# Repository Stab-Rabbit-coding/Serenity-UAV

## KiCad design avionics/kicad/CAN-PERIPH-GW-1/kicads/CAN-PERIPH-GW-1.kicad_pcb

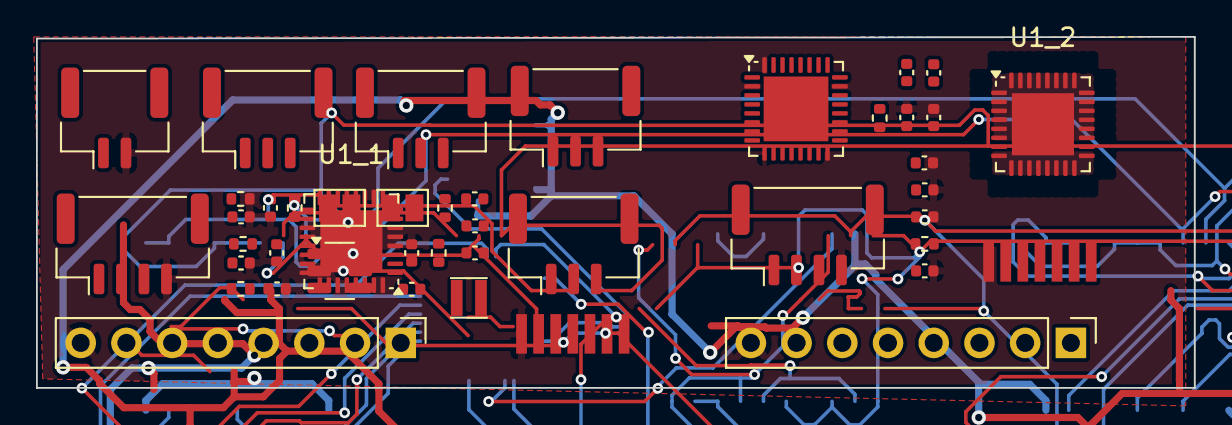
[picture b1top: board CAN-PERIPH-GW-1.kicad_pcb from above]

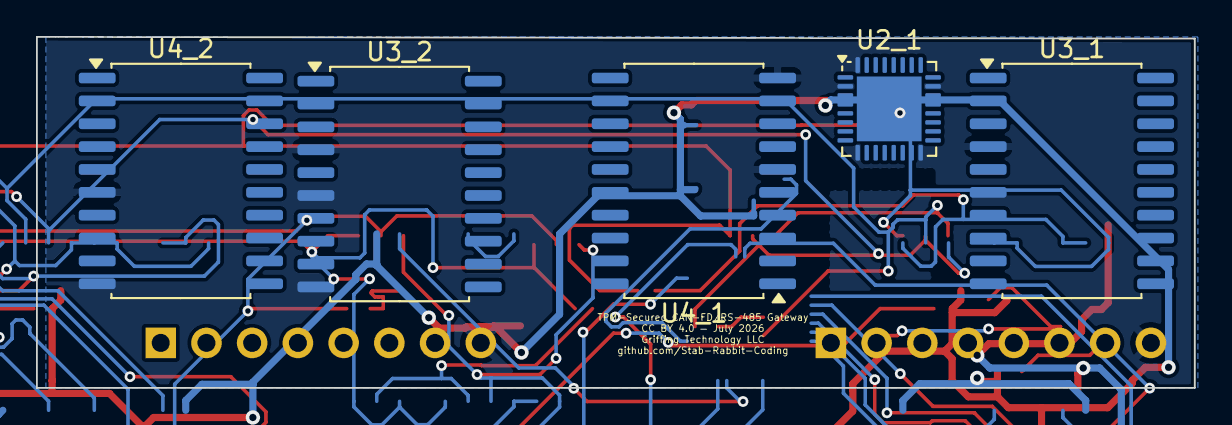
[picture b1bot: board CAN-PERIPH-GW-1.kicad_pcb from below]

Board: 2 copper layers, 64.3 x 19.5 mm, 49 parts (6 on the bottom side), 71 nets.

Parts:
C_IN: 10uF; C_0402_1005Metric
C_ISO1_1, C_ISO1_2: 100nF; C_0402_1005Metric
C_ISO2_1, C_ISO2_2: 1uF; C_0402_1005Metric
C_MCU1_1, C_MCU1_2: 100nF; C_0402_1005Metric
C_OUT: 22uF; C_0402_1005Metric
C_RS1_1, C_RS1_2, C_RS2_1, C_RS2_2: 100nF; C_0402_1005Metric
C_TPM1_1, C_TPM1_2: 100nF; C_0402_1005Metric
C_TPM2_1, C_TPM2_2: 1uF; C_0402_1005Metric
C_VCORE_1, C_VCORE_2: 1uF; C_0402_1005Metric
J_CAN_IN: CAN-FD IN; JST_GH_BM03B-GHS-TBT_1x03-1MP_P1.25mm_Vertical
J_CAN_OUT: CAN-FD OUT; JST_GH_BM03B-GHS-TBT_1x03-1MP_P1.25mm_Vertical
J_ENC_1, J_ENC_2: AK7455 pigtail; Pigtail_7W_DirectSolder
J_FLEX_1, J_FLEX_2: UART/TTL/PWM/BSHOT; PinHeader_1x08_P2.54mm_Vertical
J_PWR: +5V/GND; JST_GH_BM02B-GHS-TBT_1x02-1MP_P1.25mm_Vertical
J_RS485_IN: RS485 IN; JST_GH_BM03B-GHS-TBT_1x03-1MP_P1.25mm_Vertical
J_RS485_OUT: RS485 OUT; JST_GH_BM03B-GHS-TBT_1x03-1MP_P1.25mm_Vertical
J_SWD_1, J_SWD_2: SWD; JST_GH_BM04B-GHS-TBT_1x04-1MP_P1.25mm_Vertical
L1: 2.2uH; L_Taiyo-Yuden_NR-20xx
R_485TERM: 120R; R_0402_1005Metric
R_CANTERM: 120R; R_0402_1005Metric
R_FBB: 20k; R_0402_1005Metric
R_FBT: 10k; R_0402_1005Metric
R_NRST_1, R_NRST_2: 10k; R_0402_1005Metric
R_TPM_RST_1, R_TPM_RST_2: 10k; R_0402_1005Metric
SJ1, SJ2: open; SolderJumper-2_P1.3mm_Open_Pad1.0x1.5mm
U1_1, U1_2: TI MSPM0G3518-Q1; Texas_RHB0032E_VQFN-32-1EP_5x5mm_P0.5mm_EP3.45x3.45mm
U2_1, U2_2: Infineon SLB 9672AU2.0; QFN-32-1EP_5x5mm_P0.5mm_EP3.6x3.6mm
U3_1, U3_2: ISOW1044BDFMR; SOIC-20W_7.5x12.8mm_P1.27mm
U4_1, U4_2: ISOW1412; SOIC-20W_7.5x12.8mm_P1.27mm
U_REG_3V3: TLV62569DBVR; SOT-23-6

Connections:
+3V3: C_ISO1_1.1, C_ISO1_2.1, C_MCU1_1.1, C_MCU1_2.1, C_OUT.1, C_RS1_1.1, C_RS1_2.1, C_TPM1_1.1, C_TPM1_2.1, C_TPM2_1.1, C_TPM2_2.1, J_ENC_1.6, J_ENC_2.6, J_FLEX_1.7, J_FLEX_2.7, L1.2, R_FBT.1, R_NRST_1.1, R_NRST_2.1, R_TPM_RST_1.1, R_TPM_RST_2.1, U1_1.4, U1_2.4, U2_1.1, U2_1.8, U2_1.14, U2_1.22, U2_2.1, U2_2.8, U2_2.14, U2_2.22, U3_1.1, U3_1.9, U3_2.1, U3_2.9, U4_1.1, U4_1.9, U4_2.1, U4_2.9
+5V: C_IN.1, J_FLEX_1.6, J_FLEX_2.6, J_PWR.1, U_REG_3V3.1, U_REG_3V3.4
CANFD_FLT_N_1: U1_1.27, U3_1.8
CANFD_FLT_N_2: U1_2.27, U3_2.8
CANFD_RX_1: U1_1.17, U3_1.5
CANFD_RX_2: U1_2.17, U3_2.5
CANFD_TX_1: U1_1.16, U3_1.3
CANFD_TX_2: U1_2.16, U3_2.3
CANTERM_MID: R_CANTERM.2, SJ1.1
CAN_H: J_CAN_IN.1, J_CAN_OUT.1, R_CANTERM.1, U3_1.19, U3_2.19
CAN_L: J_CAN_IN.2, J_CAN_OUT.2, SJ1.2, U3_1.18, U3_2.18
ENC_ERROR_1: J_ENC_1.7, U1_1.18
ENC_ERROR_2: J_ENC_2.7, U1_2.18
ENC_SPI_CS_1: J_ENC_1.2, U1_1.19
ENC_SPI_CS_2: J_ENC_2.2, U1_2.19
ENC_SPI_MISO_1: J_ENC_1.5, U1_1.20
ENC_SPI_MISO_2: J_ENC_2.5, U1_2.20
ENC_SPI_MOSI_1: J_ENC_1.4, U1_1.22
ENC_SPI_MOSI_2: J_ENC_2.4, U1_2.22
ENC_SPI_SCK_1: J_ENC_1.3, U1_1.21
ENC_SPI_SCK_2: J_ENC_2.3, U1_2.21
FLEX_BSHOT_IO_1: J_FLEX_1.5, U1_1.30
FLEX_BSHOT_IO_2: J_FLEX_2.5, U1_2.30
FLEX_PWM_IO_1: J_FLEX_1.4, U1_1.29
FLEX_PWM_IO_2: J_FLEX_2.4, U1_2.29
FLEX_TTL_GPIO_1: J_FLEX_1.3, U1_1.28
FLEX_TTL_GPIO_2: J_FLEX_2.3, U1_2.28
FLEX_UART_RX_1: J_FLEX_1.2, U1_1.2
FLEX_UART_RX_2: J_FLEX_2.2, U1_2.2
FLEX_UART_TX_1: J_FLEX_1.1, U1_1.1
FLEX_UART_TX_2: J_FLEX_2.1, U1_2.1
GND: C_IN.2, C_ISO1_1.2, C_ISO1_2.2, C_MCU1_1.2, C_MCU1_2.2, C_OUT.2, C_RS1_1.2, C_RS1_2.2, C_TPM1_1.2, C_TPM1_2.2, C_TPM2_1.2, C_TPM2_2.2, C_VCORE_1.2, C_VCORE_2.2, J_ENC_1.1, J_ENC_2.1, J_FLEX_1.8, J_FLEX_2.8, J_PWR.2, J_SWD_1.4, J_SWD_2.4, R_FBB.2, U1_1.5, U1_1.33, U1_2.5, U1_2.33, U2_1.2, U2_1.9, U2_1.16, U2_1.23, U2_1.32, U2_1.33, U2_2.2, U2_2.9, U2_2.16, U2_2.23, U2_2.32, U2_2.33, U3_1.4, U3_1.6, U3_1.10, U3_2.4, U3_2.6, U3_2.10, U4_1.6, U4_1.10, U4_2.6, U4_2.10, U_REG_3V3.2
ISO_3V3_485_1: C_RS2_1.1, U4_1.12, U4_1.16
ISO_3V3_485_2: C_RS2_2.1, U4_2.12, U4_2.16
ISO_5V_CAN_1: C_ISO2_1.1, U3_1.12, U3_1.13, U3_1.20
ISO_5V_CAN_2: C_ISO2_2.1, U3_2.12, U3_2.13, U3_2.20
ISO_GND_485: C_RS2_1.2, C_RS2_2.2, J_RS485_IN.3, J_RS485_OUT.3, U4_1.11, U4_1.13, U4_1.15, U4_2.11, U4_2.13, U4_2.15
ISO_GND_CAN: C_ISO2_1.2, C_ISO2_2.2, J_CAN_IN.3, J_CAN_OUT.3, U3_1.11, U3_1.15, U3_1.16, U3_1.17, U3_2.11, U3_2.15, U3_2.16, U3_2.17
MCU_NRST_1: J_SWD_1.3, R_NRST_1.2, U1_1.3
MCU_NRST_2: J_SWD_2.3, R_NRST_2.2, U1_2.3
MCU_SWCLK_1: J_SWD_1.2, U1_1.24
MCU_SWCLK_2: J_SWD_2.2, U1_2.24
MCU_SWDIO_1: J_SWD_1.1, U1_1.23
MCU_SWDIO_2: J_SWD_2.1, U1_2.23
MCU_VCORE_1: C_VCORE_1.1, U1_1.32
MCU_VCORE_2: C_VCORE_2.1, U1_2.32
RS485_A: J_RS485_IN.1, J_RS485_OUT.1, R_485TERM.1, U4_1.17, U4_1.20, U4_2.17, U4_2.20
RS485_B: J_RS485_IN.2, J_RS485_OUT.2, SJ2.2, U4_1.18, U4_1.19, U4_2.18, U4_2.19
RS485_DE_1: U1_1.25, U4_1.3, U4_1.5
RS485_DE_2: U1_2.25, U4_2.3, U4_2.5
RS485_FLT_N_1: U1_1.26, U4_1.8
RS485_FLT_N_2: U1_2.26, U4_2.8
RS485_RX_1: U1_1.13, U4_1.4
RS485_RX_2: U1_2.13, U4_2.4
RS485_TX_1: U1_1.12, U4_1.2
RS485_TX_2: U1_2.12, U4_2.2
TERM485_MID: R_485TERM.2, SJ2.1
TPM_PIRQ_1: U1_1.7, U2_1.18
TPM_PIRQ_2: U1_2.7, U2_2.18
TPM_RESET_N_1: R_TPM_RST_1.2, U1_1.11, U2_1.17
TPM_RESET_N_2: R_TPM_RST_2.2, U1_2.11, U2_2.17
TPM_SPI_CS_1: U1_1.6, U2_1.20
TPM_SPI_CS_2: U1_2.6, U2_2.20
TPM_SPI_MISO_1: U1_1.8, U2_1.24
TPM_SPI_MISO_2: U1_2.8, U2_2.24
TPM_SPI_MOSI_1: U1_1.9, U2_1.21
TPM_SPI_MOSI_2: U1_2.9, U2_2.21
TPM_SPI_SCK_1: U1_1.10, U2_1.19
TPM_SPI_SCK_2: U1_2.10, U2_2.19
U_REG_FB: R_FBB.1, R_FBT.2, U_REG_3V3.5
U_REG_SW: L1.1, U_REG_3V3.3

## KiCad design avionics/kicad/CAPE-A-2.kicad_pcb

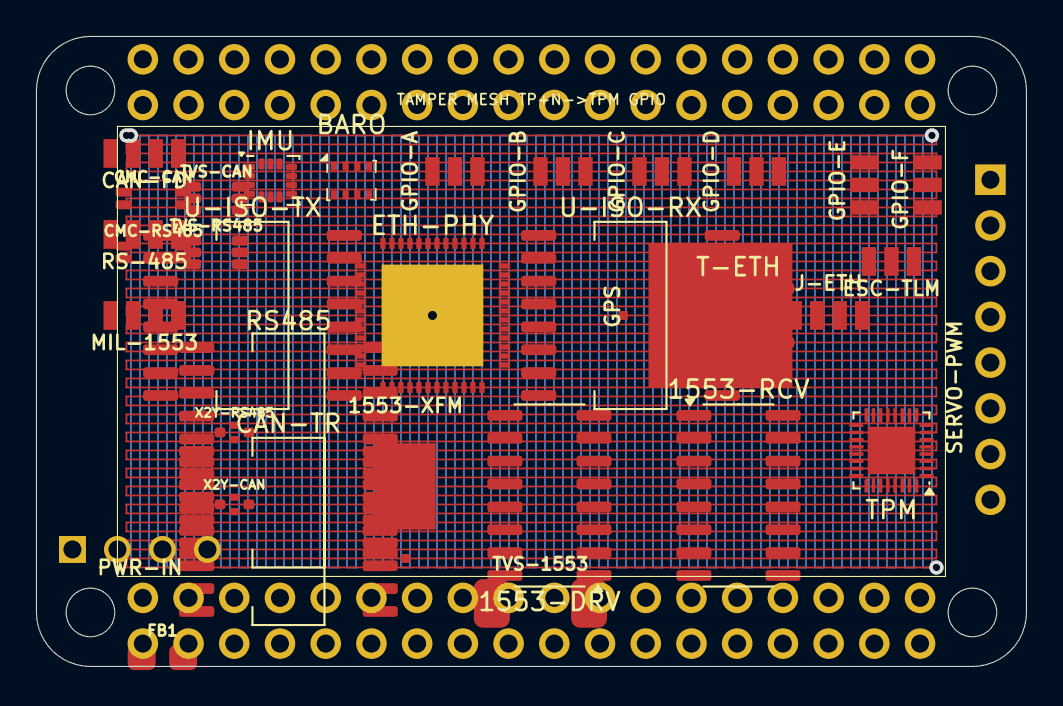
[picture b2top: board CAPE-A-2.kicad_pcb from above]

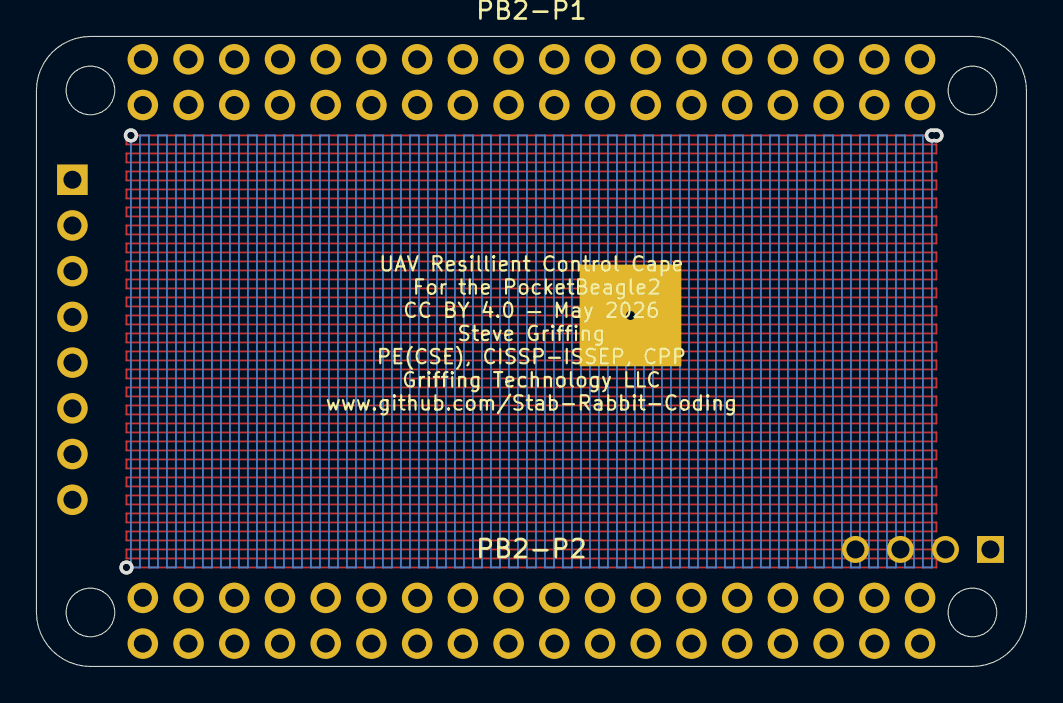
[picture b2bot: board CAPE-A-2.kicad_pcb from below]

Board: 4 copper layers, 55.0 x 35.0 mm, 36 parts (2 on the bottom side), 51 nets.

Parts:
1553-DRV: DS26LV31; SOIC-16_3.9x9.9mm_P1.27mm
1553-RCV: DS26LV32; SOIC-16_3.9x9.9mm_P1.27mm
1553-XFM: SM-1553-11; Package
BARO: BMP388; Bosch_LGA-8_2x2.5mm_P0.65mm_ClockwisePinNumbering
CAN-FD: JST-GH-4P-CAN; JST_GH_4P
CAN-TR: ISOW1044BDFMR; SOIC-16W_7.5x10.3mm_P1.27mm
CMC-CAN: SRF2012-100Y; Bourns_SRF2012_4T
CMC-RS485: SRF2012-100Y; Bourns_SRF2012_4T
ESC-TLM: JST-GH-3P-ESC-TELEM; JST_GH_3P
ETH-PHY: ADIN1300BCPZ; QFN-48-1EP_7x7mm_P0.5mm_EP5.65x5.65mm
FB1: 742792512; C_0805_2012Metric
GPIO-A: JST-GH-3P-GPIO; JST_GH_3P_V
GPIO-B: JST-GH-3P-GPIO; JST_GH_3P_V
GPIO-C: JST-GH-3P-GPIO; JST_GH_3P_V
GPIO-D: JST-GH-3P-GPIO; JST_GH_3P_V
GPIO-E: JST-GH-3P-GPIO; JST_GH_3P_V
GPIO-F: JST-GH-3P-GPIO; JST_GH_3P_V
GPS: SAM-M10Q-00B; Package
IMU: ICM-42688-P; LGA-14_3x2.5mm_P0.5mm_LayoutBorder3x4y
J-ETH: JST-GH-4P-ETH; JST_GH_4P
MIL-1553: JST-GH-4P-1553; JST_GH_4P
PB2-P1: PB2I-P1-2x18; 2x18_P1_Socket
PB2-P2: PB2I-P2-2x18; 2x18_P2_Socket
PWR-IN: Nano-Fit-4P-POWER; Connector_Molex_NanoFit
RS485: ADM2795EBRWZ; SOIC-20W_7.5x12.8mm_P1.27mm
RS-485: JST-GH-4P-RS485; JST_GH_4P
SERVO-PWM: 1x8-SERVO-PWM; Connector_PinHeader_2.54mm
T-ETH: 749010012A; ETH_XFMR_8P_5x3.5mm
TPM: SLB9670; QFN-32-1EP_4x4mm_P0.4mm_EP2.65x2.65mm
TVS-1553: SMAJ33CA; DO-214AC_SMA
TVS-CAN: PRTR5V0U2X; SOT-363_SC-88
TVS-RS485: PRTR5V0U2X; SOT-363_SC-88
U-ISO-RX: ISO7642FDWRR; SOIC-16W_7.5x10.3mm_P1.27mm
U-ISO-TX: ISO7642FDWRR; SOIC-16W_7.5x10.3mm_P1.27mm
X2Y-CAN, X2Y-RS485: 4.7nF X2Y; X2Y_Cap_4T_0402

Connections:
+3V3: CAN-TR.1, PB2-P1.33, PB2-P1.34, RS485.1, U-ISO-RX.16, U-ISO-TX.1
+5V: FB1.1, FB1.2, PB2-P1.35, PB2-P2.35
CAN_H: CAN-TR.9, CMC-CAN.1, CMC-CAN.3, TVS-CAN.1
CAN_L: CAN-TR.10, CMC-CAN.2, CMC-CAN.4, TVS-CAN.3
CAN_STB: CAN-TR.3, PB2-P1.14
ETH_LINE_RXN: J-ETH.4, T-ETH.8
ETH_LINE_RXP: J-ETH.3, T-ETH.7
ETH_LINE_TXN: J-ETH.2, T-ETH.6
ETH_LINE_TXP: J-ETH.1, T-ETH.5
ETH_RXN: ETH-PHY.5, T-ETH.4
ETH_RXP: ETH-PHY.4, T-ETH.3
ETH_TXN: ETH-PHY.2, T-ETH.2
ETH_TXP: ETH-PHY.1, T-ETH.1
GND: CAN-TR.8, ETH-PHY.3, ETH-PHY.6, ETH-PHY.10, ETH-PHY.11, ETH-PHY.12, ETH-PHY.49, PB2-P1.1, PB2-P1.2, PB2-P1.36, PB2-P2.36, RS485.2, RS485.7, RS485.8, TVS-1553.1, U-ISO-RX.9, U-ISO-TX.8, X2Y-CAN.1, X2Y-CAN.2, X2Y-CAN.3, X2Y-RS485.1, X2Y-RS485.2, X2Y-RS485.3
GND2_CAN: CAN-TR.12, CAN-TR.13, TVS-CAN.2, X2Y-CAN.4
GND2_ETH: ETH-PHY.21, ETH-PHY.22, ETH-PHY.25, ETH-PHY.34, ETH-PHY.36, U-ISO-RX.8, U-ISO-TX.9
GND2_RS485: RS485.12, RS485.13, RS485.18, RS485.19, TVS-RS485.2, X2Y-RS485.4
IMU_INT2: IMU.14, PB2-P1.18
MCAN0_RX: CAN-TR.4, PB2-P1.15
MCAN0_TX: CAN-TR.2, PB2-P1.16
MDC: ETH-PHY.19, PB2-P2.18, U-ISO-TX.6, U-ISO-TX.11
MDIO: ETH-PHY.18, PB2-P2.17, U-ISO-RX.7, U-ISO-RX.10
PHY1_INTRN: ETH-PHY.20, PB2-P2.16, U-ISO-RX.6, U-ISO-RX.11
PHY1_RSTN: ETH-PHY.35, PB2-P2.15, U-ISO-TX.7, U-ISO-TX.10
PRU_1553_RX_N: 1553-RCV.13, PB2-P1.7
PRU_1553_TX_N: 1553-DRV.6, PB2-P1.9
PRU_1553_TX_P: 1553-DRV.10, PB2-P1.10
RMII0_CRS_DV: ETH-PHY.32, PB2-P2.29, U-ISO-RX.4, U-ISO-RX.13
RMII0_REF_CLK: ETH-PHY.29, PB2-P2.27, U-ISO-TX.2, U-ISO-TX.15
RMII0_RXD0: ETH-PHY.30, PB2-P2.31, U-ISO-RX.2, U-ISO-RX.15
RMII0_RXD1: ETH-PHY.31, PB2-P2.30, U-ISO-RX.3, U-ISO-RX.14
RMII0_RX_ER: ETH-PHY.33, PB2-P2.28, U-ISO-RX.5, U-ISO-RX.12
RMII0_TXD0: ETH-PHY.28, PB2-P2.34, U-ISO-TX.3, U-ISO-TX.14
RMII0_TXD1: ETH-PHY.27, PB2-P2.33, U-ISO-TX.4, U-ISO-TX.13
RMII0_TX_EN: ETH-PHY.26, PB2-P2.32, U-ISO-TX.5, U-ISO-TX.12
RS485_A: CMC-RS485.1, CMC-RS485.3, RS485.14, TVS-RS485.1
RS485_B: CMC-RS485.2, CMC-RS485.4, RS485.15, TVS-RS485.3
RS485_DE: PB2-P1.11, RS485.4, RS485.5
RS485_RX: PB2-P1.12, RS485.6
RS485_TX: PB2-P1.13, RS485.3
SPI0_CLK: BARO.6, IMU.2, PB2-P1.25, TPM.23
SPI0_CS_BARO: BARO.7, PB2-P1.22
SPI0_CS_IMU: IMU.3, PB2-P1.26
SPI0_CS_TPM: PB2-P1.21, TPM.28
SPI0_MISO: BARO.3, IMU.5, PB2-P1.23, TPM.22
SPI0_MOSI: BARO.5, IMU.1, PB2-P1.24, TPM.21
TPM_IRQN: PB2-P2.12, TPM.24
TPM_RSTN: PB2-P2.11, TPM.1
VCC2_CAN: CAN-TR.14, TVS-CAN.5
VCC2_ETH: ETH-PHY.7, ETH-PHY.8, ETH-PHY.9, ETH-PHY.40, ETH-PHY.41, U-ISO-RX.1, U-ISO-TX.16
VCC2_RS485: RS485.11, RS485.20, TVS-RS485.5

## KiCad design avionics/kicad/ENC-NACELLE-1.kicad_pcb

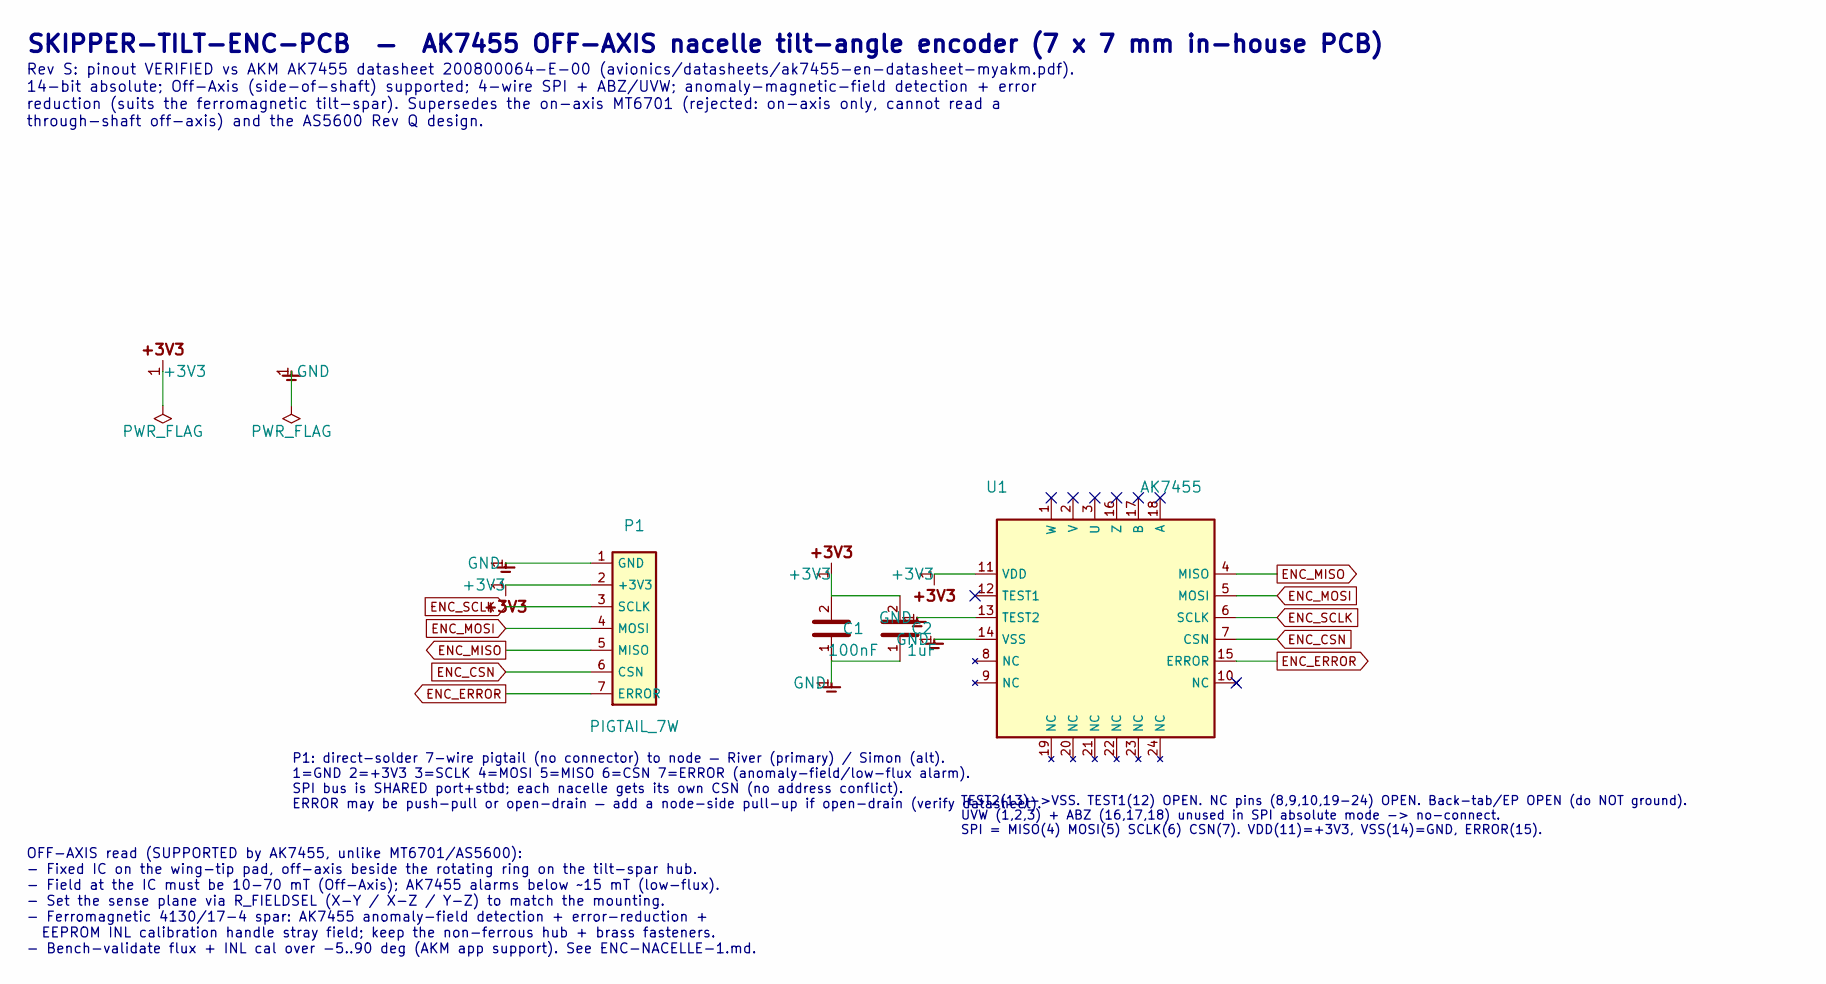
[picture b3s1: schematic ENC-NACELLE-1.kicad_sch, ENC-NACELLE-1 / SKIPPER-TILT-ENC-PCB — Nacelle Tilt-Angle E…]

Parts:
C1: 100nF; C_0402_1005Metric
C2: 1uF; C_0402_1005Metric
P1: PIGTAIL_7W; Pigtail_7W_DirectSolder
U1: AK7455; QFN-24-1EP_4x4mm_P0.5mm_EP2.6x2.6mm

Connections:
+3V3: C1.2, C2.2, P1.2 (+3V3), U1.11 (VDD)
ENC_CSN: P1.6 (CSN), U1.7 (CSN)
ENC_ERROR: P1.7 (ERROR), U1.15 (ERROR)
ENC_MISO: P1.5 (MISO), U1.4 (MISO)
ENC_MOSI: P1.4 (MOSI), U1.5 (MOSI)
ENC_SCLK: P1.3 (SCLK), U1.6 (SCLK)
GND: C1.1, C2.1, P1.1 (GND), U1.13 (TEST2), U1.14 (VSS)

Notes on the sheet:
SKIPPER-TILT-ENC-PCB — AK7455 OFF-AXIS nacelle tilt-angle encoder (7 x 7 mm in-house PCB)
Rev S: pinout VERIFIED vs AKM AK7455 datasheet 200800064-E-00 (avionics/datasheets/ak7455-en-datasheet-myakm.pdf). 14-bit absolute; Off-Axis (side-of-shaft) supported; 4-wire SPI + ABZ/UVW; anomaly-magnetic-field detection + error reduction (suits the ferromagnetic tilt-spar). Supersedes the on-axi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
P1: direct-solder 7-wire pigtail (no connector) to node — River (primary) / Simon (alt). 1=GND 2=+3V3 3=SCLK 4=MOSI 5=MISO 6=CSN 7=ERROR (anomaly-field/low-flux alarm). SPI bus is SHARED port+stbd; each nacelle gets its own CSN (no address conflict). ERROR may be push-pull or open-drain — add a nod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
TEST2(13)->VSS. TEST1(12) OPEN. NC pins (8,9,10,19-24) OPEN. Back-tab/EP OPEN (do NOT ground). UVW (1,2,3) + ABZ (16,17,18) unused in SPI absolute mode -> no-connect. SPI = MISO(4) MOSI(5) SCLK(6) CSN(7). VDD(11)=+3V3, VSS(14)=GND, ERROR(15).
OFF-AXIS read (SUPPORTED by AK7455, unlike MT6701/AS5600): - Fixed IC on the wing-tip pad, off-axis beside the rotating ring on the tilt-spar hub. - Field at the IC must be 10-70 mT (Off-Axis); AK7455 alarms below ~15 mT (low-flux). - Set the sense plane via R_FIELDSEL (X-Y / X-Z / Y-Z) to match th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

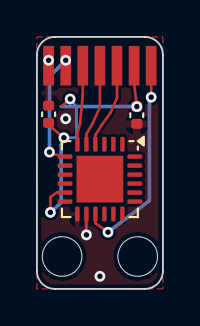
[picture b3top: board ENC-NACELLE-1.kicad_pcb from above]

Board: 2 copper layers, 7.0 x 14.0 mm, 6 parts (0 on the bottom side), 7 nets.

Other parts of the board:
MH1, MH2: M2_SELF_TAP; MountingHole_2.2mm_M2_SelfTap_Compact

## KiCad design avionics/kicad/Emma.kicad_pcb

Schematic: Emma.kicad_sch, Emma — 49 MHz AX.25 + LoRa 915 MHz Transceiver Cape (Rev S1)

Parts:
1.2k C: 10nF RX RC Bandpass 1200Hz Cap
1.2k R: 13k Ohm RX RC Bandpass 1200Hz
2.2k C: 10nF RX RC Bandpass 2200Hz Cap
2.2k R: 7.2k Ohm RX RC Bandpass 2200Hz
49M DDS: Si5351A-B-GT 49MHz DDS I2C Synthesiser
+3V 10n: 10nF C0G 0402 +3V3 VHF 49MHz Bypass
+3V 10u: 10uF X5R 0805 +3V3 Mid-freq
+3V 100n: 100nF X7R 0402 +3V3 HF Bypass
+3V 100u: 100uF 10V X5R 1210 +3V3 Bulk
+5V 100n: 100nF X7R 0402 +5V HF Bypass
+5V 100u: 100uF 10V X5R 1210 +5V Bulk
+5V Bead: 742792512
AFSK Cp: 1uF AFSK Audio Coupling DAC→PA
ANT CMC: SRF2012-100Y
ANT RPSMA: RPSMA-EDGE-50R
ANT TVS: PRTR5V0U2X
C1 120p: 120pF C0G LPF Shunt-1
C2 180p: 180pF C0G LPF Shunt-2
C3 120p: 120pF C0G LPF Shunt-3
CMP By: 100nF +3V3 U2B CMP Bypass
C_INV: 100nF C0G 0402 INV1 VCC Bypass
C_MUX: 100nF C0G 0402 MUX1 VCC Bypass
DAC By: 100nF +3V3 U2A DAC Bypass
ETH-PHY: ADIN1300BCPZ
GND X2Y: 4.7nF_X2Y_C0G
INV1: SN74LVC1G04 SOT-23-5 3.3V UART_RX_F->SBUS_OUT
J-ETH: JST-GH-4P-ETH
L1 100n: 100nH Coilcraft-0805HQ-101J LPF Series-1
L2 180n: 180nH Coilcraft-0805HQ-181J LPF Series-2
L3 180n: 180nH Coilcraft-0805HQ-181J LPF Series-3
LDO 3V3: MCP1703T-3302 LDO 3.3V 72dB-PSRR@100kHz
LDO By: 100nF +3V3 U6 LDO Bypass
LNA: MGA-82563 LNA 2.4dB NF 50-6000MHz
LNA By: 100nF +3V3 U4 LNA Bypass
LoRa: RFM95W
MUX1: SN74LVC1G157 SC-70-6 2:1MUX UART/SBUS Select
OSC By: 100nF +3V3 X1 TCXO Bypass
PA 100mW: 2N3866 NPN BJT PA Class-AB Final 100mW
PA By: 100nF +5V U3 PA VCC Bypass
PA By2: 1nF U3B Collector RF Bypass
PA Cb1: 100pF DDS-RF Coupling Cap to U3A
PA Cb2: 100pF PA Interstage Bypass
PA Drvr: MMBT2222A NPN BJT PA Class-A Driver
PA Rb1: 10k Ohm U3A Base Bias Resistor
PA Rb2: 1k Ohm U3B Base Bias Resistor
PA Rc1: 100 Ohm U3A Collector Load
PA Re: 10 Ohm U3B Emitter Degeneration
PB2-P1: PB2I-P1-2x18
PB2-P2: PB2I-P2-2x18
PGND 10n: 10nF C0G 0402 GND-PGND Moat Bridge
PTT Bead: 742792510 0402 Ferrite Bead 600Ohm@100MHz
RSSI Hi: 10k Ohm RSSI Scale Upper
RSSI Lo: 10k Ohm RSSI Scale Lower
RSSI_CBY: 100nF RSSI_CMP VCC Bypass
RSSI_CMP: LMV331 RSSI Carrier-Detect Comparator
RSSI_RH: 100k RSSI DCD Threshold Upper
RSSI_RL: 100k RSSI DCD Threshold Lower
RX Bead: 742792510 0402 Ferrite Bead 600Ohm@100MHz
RX Demod: LM393 Comparator RX-AFSK Demodulator
R_MODE: 10k Ohm MODE_SEL Pull-Down UART=default
S1: SPST-SMD OPEN=UART CLOSED=SBUS
SMA ESD: SMAJ5.0A Bidirectional TVS 5V Antenna ESD
SW By: 100nF +3V3 U5 Switch Bypass
T-ETH: 749010012A
T/R Sw: PE4259-63 SPDT TX/RX Switch ≥35dB isolation
TCXO 25M: TG2520SMN 25MHz TCXO ±0.5ppm
TX Bead: 742792510 0402 Ferrite Bead 600Ohm@100MHz
TX DAC: MCP4921 12-bit SPI DAC TX-AFSK Audio
Th Hi: 10k Ohm LM393 Threshold Upper
Th Lo: 10k Ohm LM393 Threshold Lower
U1 ByA: 100nF +3V3 U1-VDDA Bypass
U1 ByB: 100nF +3V3 U1-VDD Bypass
UART CMC: SRF2012-100Y CMC UART TX/RX Pair 10uH
UART TVS: PRTR5V0U2X Dual TVS 5.5V UART-TX/RX ESD

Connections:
+3V3: 49M DDS.1 (+3V3), 49M DDS.10 (+3V3), +3V 10n.1 (+3V3), +3V 10u.1 (+3V3), +3V 100n.1 (+3V3), +3V 100u.1 (+3V3), CMP By.1 (+3V3), C_INV.1 (+3V3), C_MUX.1 (+3V3), DAC By.1 (+3V3), INV1.4 (+3V3), LDO 3V3.3 (+3V3), LDO 3V3.4 (+3V3), LDO By.1 (+3V3), LNA.4 (+3V3), LNA By.1 (+3V3), MUX1.4 (+3V3), OSC By.1 (+3V3), PB2-P1.33 (+3V3), PB2-P1.34 (+3V3), RSSI_CBY.1 (+3V3), RSSI_CMP.2 (+3V3), RSSI_RH.1 (+3V3), RX Demod.2 (+3V3), S1.1 (+3V3), SW By.1 (+3V3), TCXO 25M.1 (+3V3), TCXO 25M.4 (+3V3), TX DAC.1 (+3V3), TX DAC.6 (+3V3), Th Hi.1 (+3V3), U1 ByA.1 (+3V3), U1 ByB.1 (+3V3)
+5V: +5V Bead.1 (+5V), PB2-P1.35 (+5V), PB2-P2.35 (+5V)
+5V_FILT: +5V 100n.1 (+5V_FILT), +5V 100u.1 (+5V_FILT), +5V Bead.2 (+5V_FILT), LDO 3V3.1 (+5V_FILT), PA By.1 (+5V_FILT), PA Rb1.1 (+5V_FILT), PA Rc1.1 (+5V_FILT)
AFSK_IN: AFSK Cp.2 (AFSK_IN), RX Demod.1 (AFSK_IN)
AFSK_OUT: AFSK Cp.1 (AFSK_OUT), TX DAC.7 (AFSK_OUT)
ANT: ANT CMC.1, ANT CMC.2, ANT RPSMA.1 (ANT), ANT TVS.2 (ANT), SMA ESD.1 (ANT)
CAN_STB: PB2-P1.12 (CAN_STB)
COMP_IN: 1.2k C.1 (COMP_IN), 1.2k R.2 (COMP_IN), 2.2k C.1 (COMP_IN), 2.2k R.2 (COMP_IN), RX Demod.3 (COMP_IN), Th Lo.1 (COMP_IN)
DDS_CLK: 49M DDS.6 (DDS_CLK), TX DAC.3 (DDS_CLK)
DDS_DAT: 49M DDS.7 (DDS_DAT), TX DAC.4 (DDS_DAT)
DDS_FSYNC: TX DAC.2 (DDS_FSYNC)
DDS_RF: 49M DDS.3 (DDS_RF), PA Cb1.1 (DDS_RF), PA Drvr.1 (DDS_RF), PA Rb1.2 (DDS_RF)
EMMA_ETH_LINE_RXN: J-ETH.4 (EMMA_ETH_LINE_RXN), T-ETH.8 (EMMA_ETH_LINE_RXN)
EMMA_ETH_LINE_RXP: J-ETH.3 (EMMA_ETH_LINE_RXP), T-ETH.7 (EMMA_ETH_LINE_RXP)
EMMA_ETH_LINE_TXN: J-ETH.2 (EMMA_ETH_LINE_TXN), T-ETH.6 (EMMA_ETH_LINE_TXN)
EMMA_ETH_LINE_TXP: J-ETH.1 (EMMA_ETH_LINE_TXP), T-ETH.5 (EMMA_ETH_LINE_TXP)
EMMA_ETH_RXN: ETH-PHY.5 (EMMA_ETH_RXN), T-ETH.4 (EMMA_ETH_RXN)
EMMA_ETH_RXP: ETH-PHY.4 (EMMA_ETH_RXP), T-ETH.3 (EMMA_ETH_RXP)
EMMA_ETH_TXN: ETH-PHY.2 (EMMA_ETH_TXN), T-ETH.2 (EMMA_ETH_TXN)
EMMA_ETH_TXP: ETH-PHY.1 (EMMA_ETH_TXP), T-ETH.1 (EMMA_ETH_TXP)
GND: 1.2k C.2 (GND), 2.2k C.2 (GND), 49M DDS.2 (GND), 49M DDS.4 (GND), 49M DDS.5 (GND), 49M DDS.9 (GND), +3V 10n.2 (GND), +3V 10u.2 (GND), +3V 100n.2 (GND), +3V 100u.2 (GND), +5V 100n.2 (GND), +5V 100u.2 (GND), ANT RPSMA.2 (GND), ANT RPSMA.3 (GND), ANT TVS.1 (GND), ANT TVS.3 (GND), ANT TVS.4 (GND), ANT TVS.6 (GND), C1 120p.2 (GND), C2 180p.2 (GND), C3 120p.2 (GND), CMP By.2 (GND), C_INV.2 (GND), C_MUX.2 (GND), DAC By.2 (GND), ETH-PHY.3 (GND), ETH-PHY.6 (GND), ETH-PHY.10 (GND), ETH-PHY.11 (GND), ETH-PHY.12 (GND), ETH-PHY.49 (GND), GND X2Y.1, GND X2Y.2, INV1.2 (GND), LDO 3V3.2 (GND), LDO 3V3.5 (GND), LDO By.2 (GND), LNA.5 (GND), LNA.6 (GND), LNA By.2 (GND), LoRa.1 (GND), LoRa.8 (GND), LoRa.10 (GND), MUX1.2 (GND), OSC By.2 (GND), PA 100mW.2 (GND), PA By.2 (GND), PA By2.2 (GND), PA Cb2.2 (GND), PA Drvr.2 (GND), PA Re.2 (GND), PB2-P1.1 (GND), PB2-P1.2 (GND), PB2-P1.36 (GND), PB2-P2.36 (GND), PGND 10n.1, PGND 10n.2, RSSI Lo.2 (GND), RSSI_CBY.2 (GND), RSSI_CMP.4 (GND), RSSI_RL.2 (GND), RX Demod.4 (GND), RX Demod.5 (GND), R_MODE.2 (GND), SMA ESD.2 (GND), SW By.2 (GND), T/R Sw.2 (GND), T/R Sw.6 (GND), TCXO 25M.2 (GND), TX DAC.5 (GND), TX DAC.8 (GND), Th Hi.2 (GND), Th Lo.2 (GND), U1 ByA.2 (GND), U1 ByB.2 (GND), UART TVS.1 (GND), UART TVS.3 (GND), UART TVS.4 (GND), UART TVS.6 (GND)
GND2_ETH: ETH-PHY.21 (GND2_ETH), ETH-PHY.22 (GND2_ETH), ETH-PHY.25 (GND2_ETH), ETH-PHY.34 (GND2_ETH), ETH-PHY.36 (GND2_ETH)
I2C0_SCL: PB2-P1.4 (I2C0_SCL)
I2C0_SDA: PB2-P1.3 (I2C0_SDA)
LOAD_CELL_DOUT: PB2-P2.7 (LOAD_CELL_DOUT)
LOAD_CELL_SCK: PB2-P2.8 (LOAD_CELL_SCK)
LORA_DIO0: PB2-P1.20 (LORA_DIO0)
LORA_RESETN: LoRa.6 (LORA_RESETN), PB2-P1.19 (LORA_RESETN)
MCAN1_RX: PB2-P1.13 (MCAN1_RX)
MCAN1_TX: PB2-P1.14 (MCAN1_TX)
MDC: ETH-PHY.19 (MDC), PB2-P2.18 (MDC)
MDIO: ETH-PHY.18 (MDIO), PB2-P2.17 (MDIO)
MODE_SEL: MUX1.5 (MODE_SEL), R_MODE.1 (MODE_SEL), S1.2 (MODE_SEL)
PA_EMIT: PA Re.1 (PA_EMIT)
PA_INT: PA 100mW.1 (PA_INT), PA Cb1.2 (PA_INT), PA Cb2.1 (PA_INT), PA Drvr.3 (PA_INT), PA Rb2.1, PA Rb2.2, PA Rc1.2 (PA_INT)
PHY1_INTRN: PB2-P2.16 (PHY1_INTRN)
PHY1_RSTN: PB2-P2.15 (PHY1_RSTN)
PHY2_INTRN: ETH-PHY.20 (PHY2_INTRN), PB2-P2.14 (PHY2_INTRN)
PHY2_RSTN: ETH-PHY.35 (PHY2_RSTN), PB2-P2.13 (PHY2_RSTN)
PRU_1553_RX_N: PB2-P1.5 (PRU_1553_RX_N)
PRU_1553_RX_P: PB2-P1.6 (PRU_1553_RX_P)
PRU_1553_TX_N: PB2-P1.7 (PRU_1553_TX_N)
PRU_1553_TX_P: PB2-P1.8 (PRU_1553_TX_P)
PTT_N: PB2-P2.1 (PTT_N), PTT Bead.1, PTT Bead.2, T/R Sw.4 (PTT_N)
PWM_CH0: PB2-P2.6 (PWM_CH0)
PWM_CH1: PB2-P2.5 (PWM_CH1)
PWM_CH2: PB2-P2.4 (PWM_CH2)
PWM_CH3: PB2-P2.3 (PWM_CH3)
RF_ANT_SW: T/R Sw.1 (RF_ANT_SW)
RF_FILT: C3 120p.1 (RF_FILT), L3 180n.2 (RF_FILT), T/R Sw.5 (RF_FILT)
RF_LPF_N1: C1 120p.1 (RF_LPF_N1), L1 100n.2 (RF_LPF_N1), L2 180n.1 (RF_LPF_N1)
RF_LPF_N2: C2 180p.1 (RF_LPF_N2), L2 180n.2 (RF_LPF_N2), L3 180n.1 (RF_LPF_N2)
RF_RX: LNA.3 (RF_RX), T/R Sw.3 (RF_RX)
RF_TX: ANT TVS.5 (RF_TX), L1 100n.1 (RF_TX), PA 100mW.3 (RF_TX), PA By2.1 (RF_TX)
RMII0_CRS_DV: PB2-P2.29 (RMII0_CRS_DV)
RMII0_REF_CLK: PB2-P2.27 (RMII0_REF_CLK)
RMII0_RXD0: PB2-P2.31 (RMII0_RXD0)
RMII0_RXD1: PB2-P2.30 (RMII0_RXD1)
RMII0_RX_ER: PB2-P2.28 (RMII0_RX_ER)
RMII0_TXD0: PB2-P2.34 (RMII0_TXD0)
RMII0_TXD1: PB2-P2.33 (RMII0_TXD1)
RMII0_TX_EN: PB2-P2.32 (RMII0_TX_EN)
RMII1_CRS_DV: ETH-PHY.32 (RMII1_CRS_DV), PB2-P2.21 (RMII1_CRS_DV)
RMII1_REF_CLK: ETH-PHY.29 (RMII1_REF_CLK), PB2-P2.19 (RMII1_REF_CLK)
RMII1_RXD0: ETH-PHY.30 (RMII1_RXD0), PB2-P2.23 (RMII1_RXD0)
RMII1_RXD1: ETH-PHY.31 (RMII1_RXD1), PB2-P2.22 (RMII1_RXD1)
RMII1_RX_ER: ETH-PHY.33 (RMII1_RX_ER), PB2-P2.20 (RMII1_RX_ER)
RMII1_TXD0: ETH-PHY.28 (RMII1_TXD0), PB2-P2.26 (RMII1_TXD0)
RMII1_TXD1: ETH-PHY.27 (RMII1_TXD1), PB2-P2.25 (RMII1_TXD1)
RMII1_TX_EN: ETH-PHY.26 (RMII1_TX_EN), PB2-P2.24 (RMII1_TX_EN)
RS485_DE: PB2-P1.9 (RS485_DE)
RS485_RX: PB2-P1.10 (RS485_RX)
RS485_TX: PB2-P1.11 (RS485_TX)
RSSI_ANA: RSSI Hi.2 (RSSI_ANA), RSSI Lo.1 (RSSI_ANA), RSSI_CMP.1 (RSSI_ANA)
RSSI_DCD: PB2-P2.2 (RSSI_DCD), RSSI_CMP.5 (RSSI_DCD)
RSSI_RAW: LNA.2 (RSSI_RAW), RSSI Hi.1 (RSSI_RAW)
RSSI_REF: RSSI_CMP.3 (RSSI_REF), RSSI_RH.2 (RSSI_REF), RSSI_RL.1 (RSSI_REF)
RX_LNA: 1.2k R.1 (RX_LNA), 2.2k R.1 (RX_LNA), LNA.1 (RX_LNA)
SBUS_OUT: INV1.3 (SBUS_OUT), MUX1.6 (SBUS_OUT)
SDIO_CLK: PB2-P1.32 (SDIO_CLK)
SDIO_CMD: PB2-P1.31 (SDIO_CMD)
SDIO_D0: PB2-P1.30 (SDIO_D0)
SDIO_D1: PB2-P1.29 (SDIO_D1)
SDIO_D2: PB2-P1.28 (SDIO_D2)
SDIO_D3: PB2-P1.27 (SDIO_D3)
SPI1_CLK: LoRa.4 (SPI1_CLK), PB2-P1.25 (SPI1_CLK)
SPI1_CS_LORA: LoRa.5 (SPI1_CS_LORA), PB2-P1.26 (SPI1_CS_LORA)
SPI1_CS_NOR: PB2-P1.22 (SPI1_CS_NOR)
SPI1_CS_TPM: PB2-P1.21 (SPI1_CS_TPM)
SPI1_MISO: LoRa.2 (SPI1_MISO), PB2-P1.23 (SPI1_MISO)
SPI1_MOSI: LoRa.3 (SPI1_MOSI), PB2-P1.24 (SPI1_MOSI)
TCXO_OUT: 49M DDS.8 (TCXO_OUT), TCXO 25M.3 (TCXO_OUT)
TPM_IRQN: PB2-P2.12 (TPM_IRQN)
TPM_RSTN: PB2-P2.11 (TPM_RSTN)
UART_RCRS_RX: PB2-P1.15 (UART_RCRS_RX), UART CMC.1 (UART_RCRS_RX), UART TVS.2 (UART_RCRS_RX)
UART_RCRS_TX: PB2-P1.16 (UART_RCRS_TX), UART CMC.4 (UART_RCRS_TX), UART TVS.5 (UART_RCRS_TX)
UART_RX_F: INV1.1 (UART_RX_F), MUX1.1 (UART_RX_F), RX Bead.1, RX Bead.2
UART_RX_MUX: MUX1.3 (UART_RX_MUX), UART CMC.3 (UART_RX_MUX)
UART_SIK_RX: PB2-P1.17 (UART_SIK_RX)
UART_SIK_TX: PB2-P1.18 (UART_SIK_TX)
UART_TX_F: TX Bead.1, TX Bead.2, UART CMC.2 (UART_TX_F)
VCC2_ETH: ETH-PHY.7 (VCC2_ETH), ETH-PHY.8 (VCC2_ETH), ETH-PHY.9 (VCC2_ETH), ETH-PHY.40 (VCC2_ETH), ETH-PHY.41 (VCC2_ETH)
WINCH_IN1: PB2-P2.10 (WINCH_IN1)
WINCH_IN2: PB2-P2.9 (WINCH_IN2)

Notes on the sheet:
POWER SUPPLY (5V input filter, MCP1703 LDO, bypass cascade)
DDS / TCXO (Si5351A 49 MHz synthesiser)
PA CHAIN (MMBT2222A driver + 2N3866 100 mW final)
6-ELEMENT CHEBYSHEV LPF
T/R SWITCH, LNA, ANTENNA PORT
AFSK MODEM (MCP4921 TX DAC, LM393 RX demod, tone filters)
UART / SBUS DIGITAL (CMC, TVS, beads, inverter, mux)
RSSI CARRIER-DETECT (NEW 2026-07-04 — analog RSSI -> 1-bit RSSI_DCD)
LoRa 915 MHz (RFM95W, SPI via PB2-P1)
ETHERNET 2nd PORT (ADIN1300 PHY + T-ETH isolation xfmr, JST-GH-4P line)
PB2-I PASSTHROUGH RAILS (PocketBeagle 2 Industrial P1 + P2)

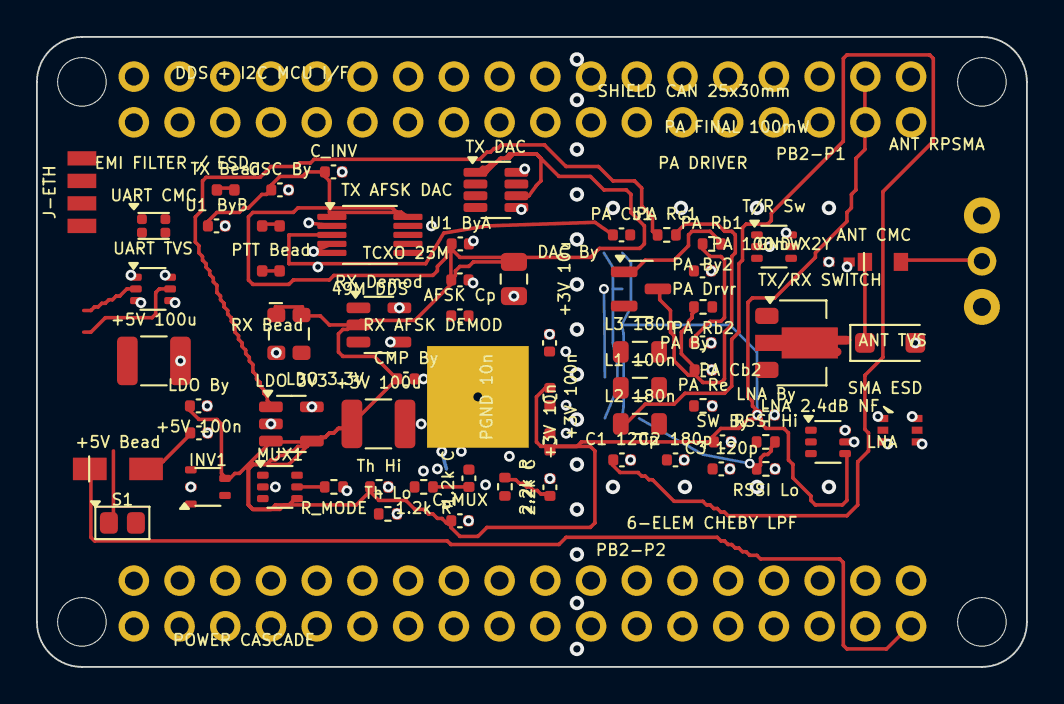
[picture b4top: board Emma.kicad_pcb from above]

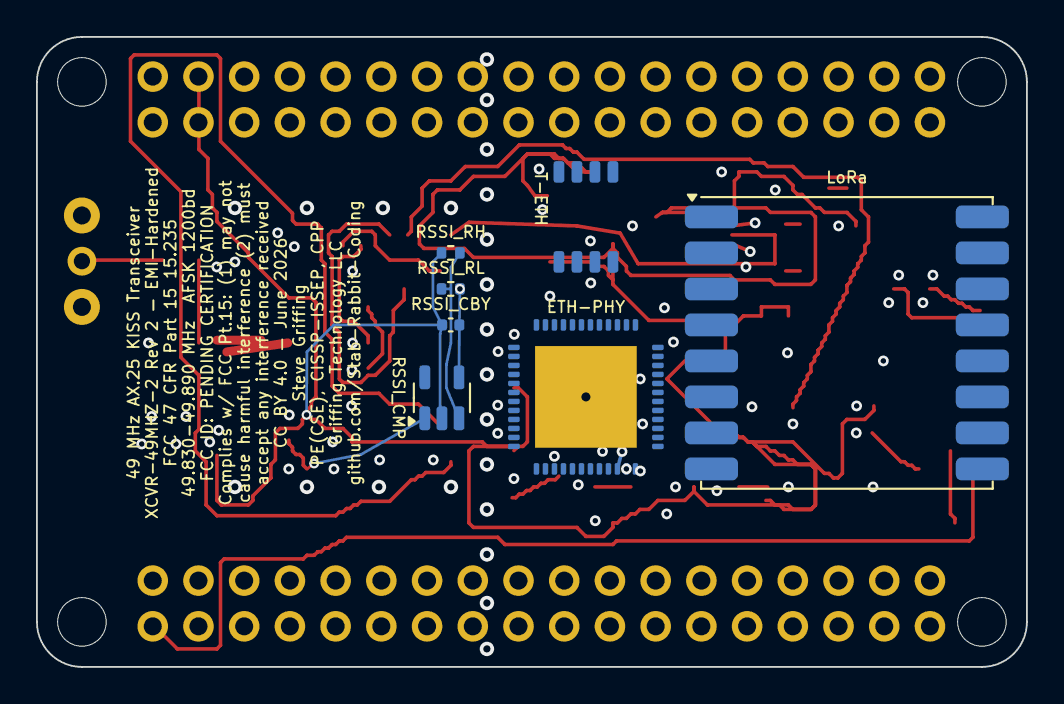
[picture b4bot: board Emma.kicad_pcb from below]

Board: 4 copper layers, 55.0 x 35.0 mm, 74 parts (7 on the bottom side), 58 nets.

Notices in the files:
avionics/kicad/Bus-Gateway/scripts/gen_can_periph_gw_sch.py:
STM32L431KCUx + NXP TJA1051TK-3) is GPL-3.0-licensed -- INCOMPATIBLE with this
project's CC BY 4.0 terms, so no VimDrones file, symbol, or schematic
Pilot/XO/Observer, not a new one-off part, and so no GPL-licensed VimDrones
License: CC BY 4.0
avionics/kicad/CAN-PERIPH-GW-1/kicads/CAN-PERIPH-GW-1.kicad_pcb:
CC BY 4.0 -- creativecommons.org/licenses/by/4.0
CC BY 4.0 — July 2026
avionics/kicad/CAPE-A-2.kicad_pcb:
Hull: Peter Farell CC BY 4.0 | Nozzle: BamJr CC BY 4.0 | Firefly/Serenity fan-work, not officially licensed
